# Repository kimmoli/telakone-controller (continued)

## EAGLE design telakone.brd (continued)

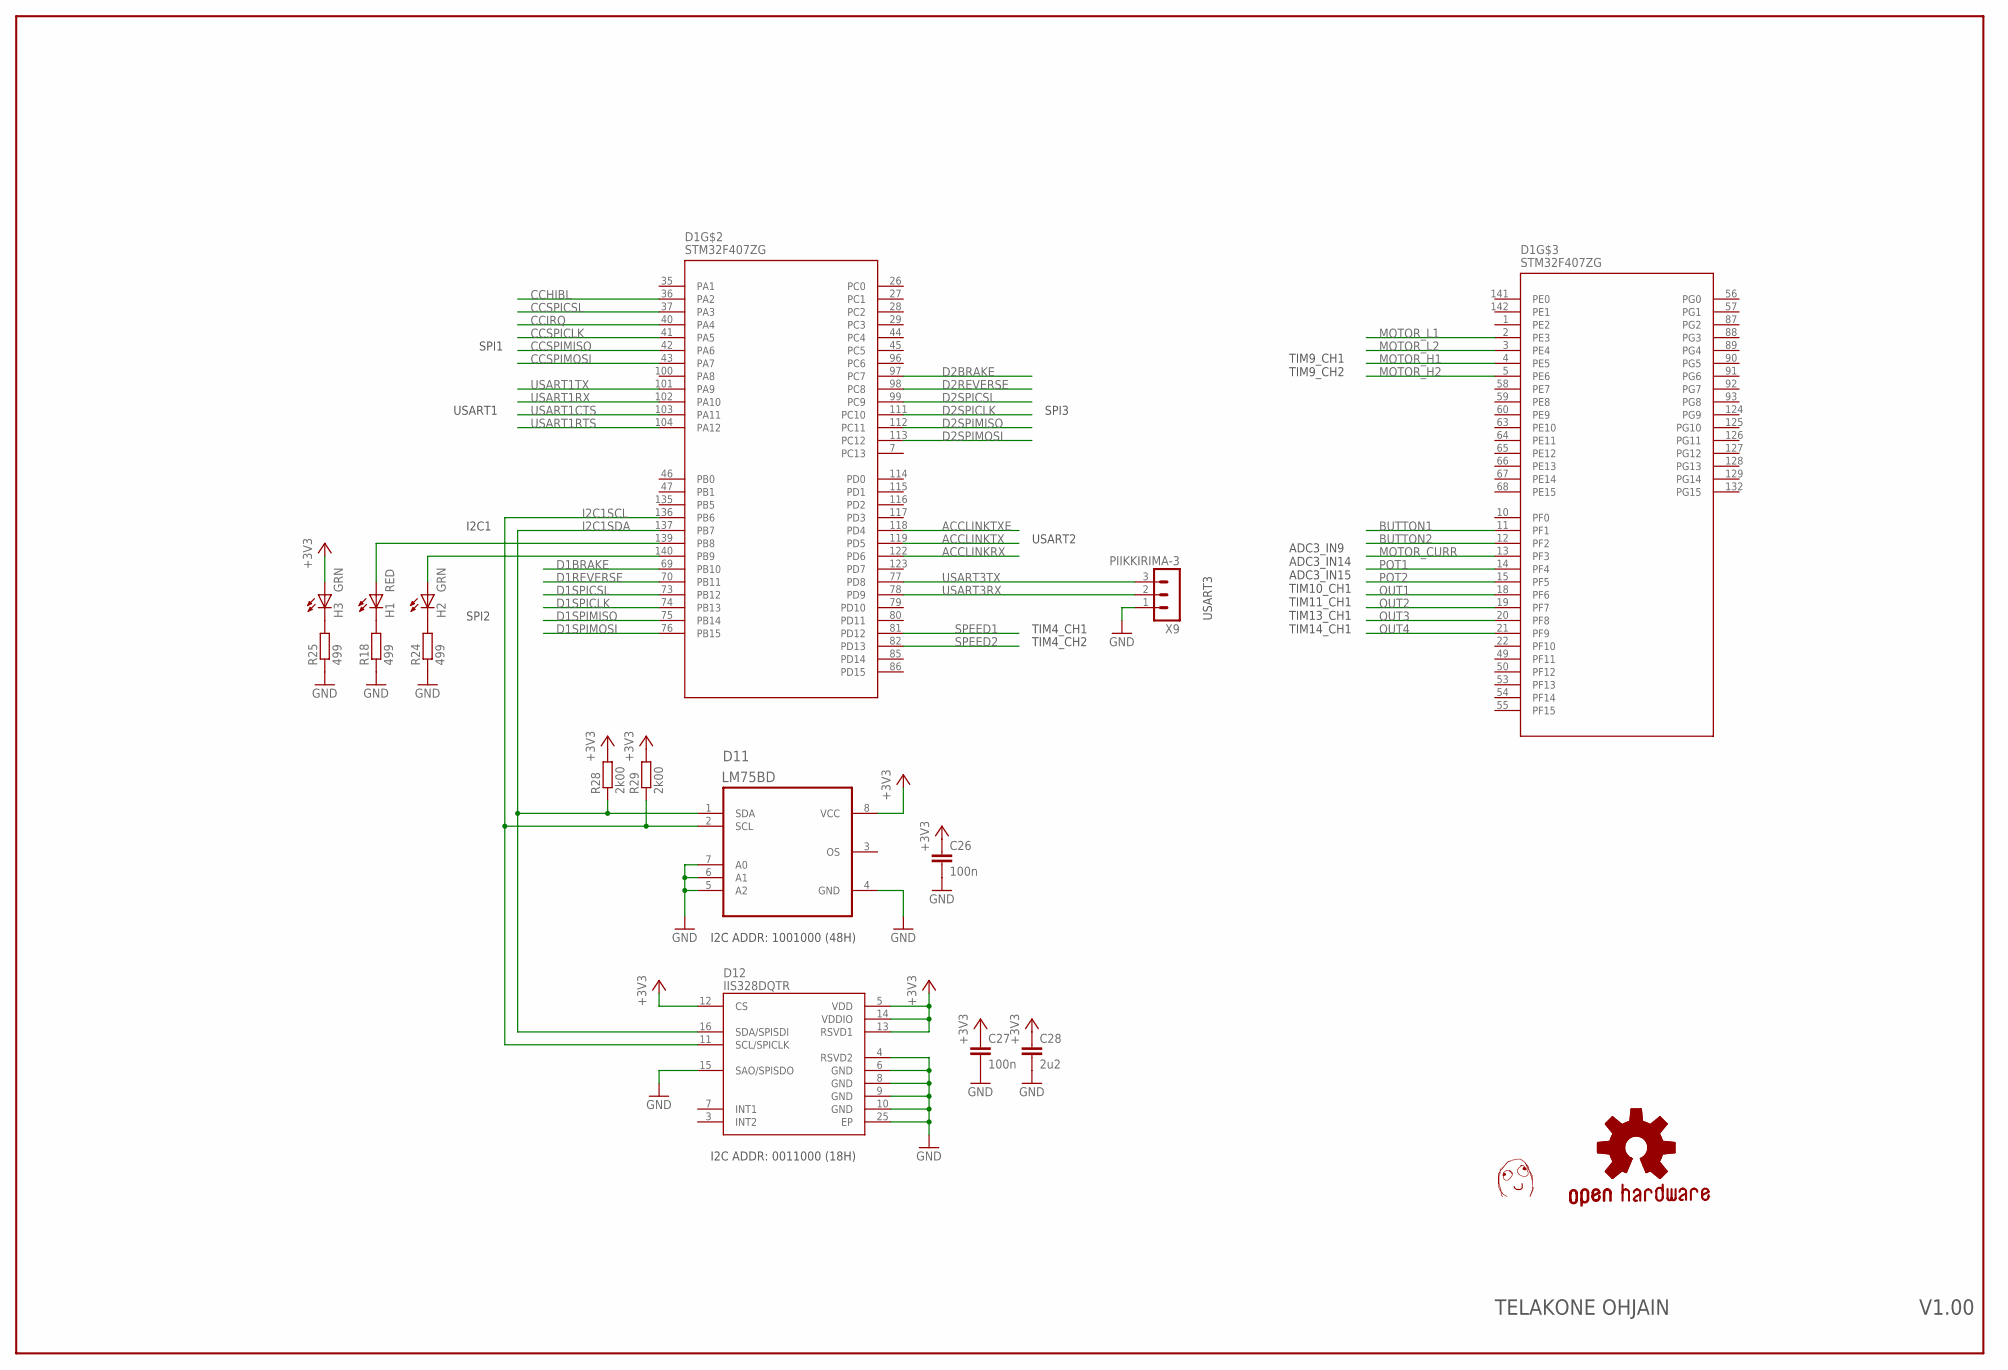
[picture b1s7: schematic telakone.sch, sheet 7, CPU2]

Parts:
C26, C27: 100n; C0603
C28: 2u2; C0603
D1: STM32F407ZG; LQFP-144
D11: LM75BD; SOIC8-N_MC
D12: IIS328DQTR; QFN50P400X400X100-25N
H1: RED; CHIP-LED0603
H2, H3: GRN; CHIP-LED0603
R18, R24, R25: 499; R0603
R28, R29: 2k00; R0603
U$13: DAFUG
X9: PIIKKIRIMA-3

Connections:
+3V3: C26.1, C27.1, C28.1, D11.8 (VCC), D12.5 (VDD), D12.12 (CS), D12.13 (RSVD1), D12.14 (VDDIO), H3.A, R28.2, R29.2; also elsewhere on the board
ACCLINKRX: D1.122 (PD6); also elsewhere on the board
ACCLINKTX: D1.119 (PD5); also elsewhere on the board
ACCLINKTXE: D1.118 (PD4); also elsewhere on the board
BUTTON1: D1.11 (PF1); also elsewhere on the board
BUTTON2: D1.12 (PF2); also elsewhere on the board
CCHIBL: D1.36 (PA2); also elsewhere on the board
CCIRQ: D1.40 (PA4); also elsewhere on the board
CCSPICLK: D1.41 (PA5); also elsewhere on the board
CCSPICSL: D1.37 (PA3); also elsewhere on the board
CCSPIMISO: D1.42 (PA6); also elsewhere on the board
CCSPIMOSI: D1.43 (PA7); also elsewhere on the board
D1BRAKE: D1.69 (PB10); also elsewhere on the board
D1REVERSE: D1.70 (PB11); also elsewhere on the board
D1SPICLK: D1.74 (PB13); also elsewhere on the board
D1SPICSL: D1.73 (PB12); also elsewhere on the board
D1SPIMISO: D1.75 (PB14); also elsewhere on the board
D1SPIMOSI: D1.76 (PB15); also elsewhere on the board
D2BRAKE: D1.97 (PC7); also elsewhere on the board
D2REVERSE: D1.98 (PC8); also elsewhere on the board
D2SPICLK: D1.111 (PC10); also elsewhere on the board
D2SPICSL: D1.99 (PC9); also elsewhere on the board
D2SPIMISO: D1.112 (PC11); also elsewhere on the board
D2SPIMOSI: D1.113 (PC12); also elsewhere on the board
GND: C26.2, C27.2, C28.2, D11.4 (GND), D11.5 (A2), D11.6 (A1), D11.7 (A0), D12.4 (RSVD2), D12.6 (GND), D12.8 (GND), D12.9 (GND), D12.10 (GND), D12.15 (SAO/SPISDO), D12.25 (EP), R18.1, R24.1, R25.1, X9.1; also elsewhere on the board
I2C1SCL: D1.136 (PB6), D11.2 (SCL), D12.11 (SCL/SPICLK), R29.1
I2C1SDA: D1.137 (PB7), D11.1 (SDA), D12.16 (SDA/SPISDI), R28.1
MOTOR_CURR: D1.13 (PF3); also elsewhere on the board
MOTOR_H1: D1.4 (PE5); also elsewhere on the board
MOTOR_H2: D1.5 (PE6); also elsewhere on the board
MOTOR_L1: D1.2 (PE3); also elsewhere on the board
MOTOR_L2: D1.3 (PE4); also elsewhere on the board
unnamed: H2.C, R24.2
unnamed: H1.C, R18.2
unnamed: D1.139 (PB8), H1.A
unnamed: D1.140 (PB9), H2.A
unnamed: H3.C, R25.2
OUT1: D1.18 (PF6); also elsewhere on the board
OUT2: D1.19 (PF7); also elsewhere on the board
OUT3: D1.20 (PF8); also elsewhere on the board
OUT4: D1.21 (PF9); also elsewhere on the board
POT1: D1.14 (PF4); also elsewhere on the board
POT2: D1.15 (PF5); also elsewhere on the board
SPEED1: D1.81 (PD12); also elsewhere on the board
SPEED2: D1.82 (PD13); also elsewhere on the board
USART1CTS: D1.103 (PA11); also elsewhere on the board
USART1RTS: D1.104 (PA12); also elsewhere on the board
USART1RX: D1.102 (PA10); also elsewhere on the board
USART1TX: D1.101 (PA9); also elsewhere on the board
USART3RX: D1.78 (PD9), X9.2
USART3TX: D1.77 (PD8), X9.3

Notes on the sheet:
SPI1
I2C ADDR: 1001000 (48H)
I2C ADDR: 0011000 (18H)
ADC3_IN9 ADC3_IN14 ADC3_IN15 TIM10_CH1 TIM11_CH1 TIM13_CH1 TIM14_CH1
TIM9_CH1 TIM9_CH2
SPI2
SPI3
I2C1
TIM4_CH1
TIM4_CH2
USART2
USART1
USART3
V1.00
TELAKONE OHJAIN

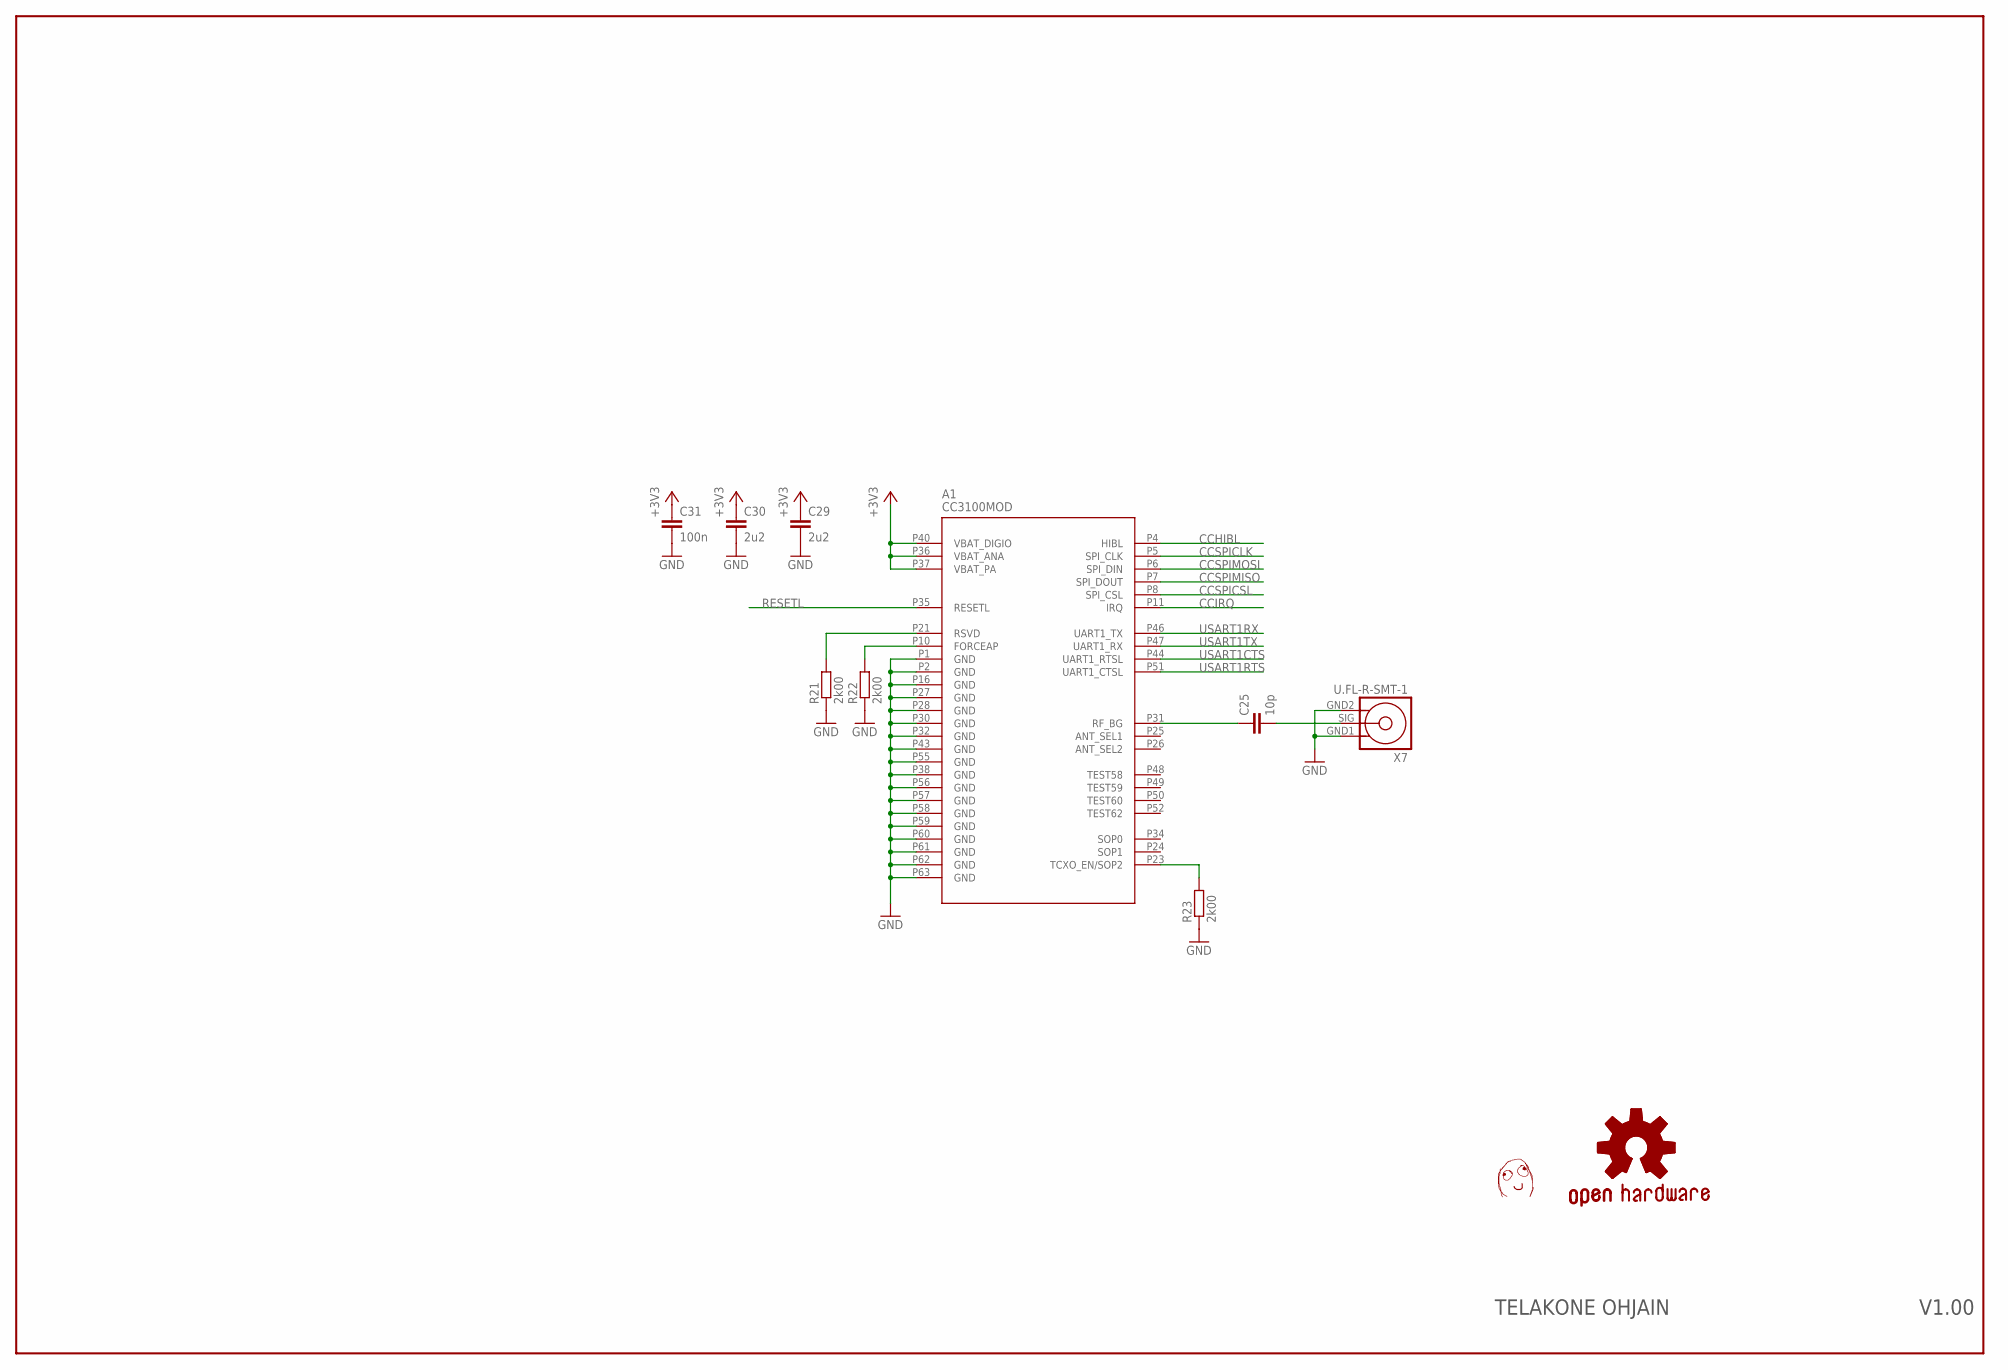
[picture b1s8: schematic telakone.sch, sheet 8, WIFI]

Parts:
A1: CC3100MOD
C25: 10p; C0603
C29, C30: 2u2; C0603
C31: 100n; C0603
R21, R22, R23: 2k00; R0603
U$15: DAFUG
X7: U.FL-R-SMT-1

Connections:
+3V3: A1.P36 (VBAT_ANA), A1.P37 (VBAT_PA), A1.P40 (VBAT_DIGIO), C29.1, C30.1, C31.1; also elsewhere on the board
CCHIBL: A1.P4 (HIBL); also elsewhere on the board
CCIRQ: A1.P11 (IRQ); also elsewhere on the board
CCSPICLK: A1.P5 (SPI_CLK); also elsewhere on the board
CCSPICSL: A1.P8 (SPI_CSL); also elsewhere on the board
CCSPIMISO: A1.P7 (SPI_DOUT); also elsewhere on the board
CCSPIMOSI: A1.P6 (SPI_DIN); also elsewhere on the board
GND: A1.P1 (GND), A1.P2 (GND), A1.P16 (GND), A1.P27 (GND), A1.P28 (GND), A1.P30 (GND), A1.P32 (GND), A1.P38 (GND), A1.P43 (GND), A1.P55 (GND), A1.P56 (GND), A1.P57 (GND), A1.P58 (GND), A1.P59 (GND), A1.P60 (GND), A1.P61 (GND), A1.P62 (GND), A1.P63 (GND), C29.2, C30.2, C31.2, R21.1, R22.1, R23.1, X7.GND1 (1), X7.GND2 (3); also elsewhere on the board
unnamed: A1.P31 (RF_BG), C25.1
unnamed: C25.2, X7.SIG (2)
unnamed: A1.P21 (RSVD), R21.2
unnamed: A1.P10 (FORCEAP), R22.2
unnamed: A1.P23 (TCXO_EN/SOP2), R23.2
RESETL: A1.P35 (RESETL); also elsewhere on the board
USART1CTS: A1.P44 (UART1_RTSL); also elsewhere on the board
USART1RTS: A1.P51 (UART1_CTSL); also elsewhere on the board
USART1RX: A1.P46 (UART1_TX); also elsewhere on the board
USART1TX: A1.P47 (UART1_RX); also elsewhere on the board

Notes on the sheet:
V1.00
TELAKONE OHJAIN

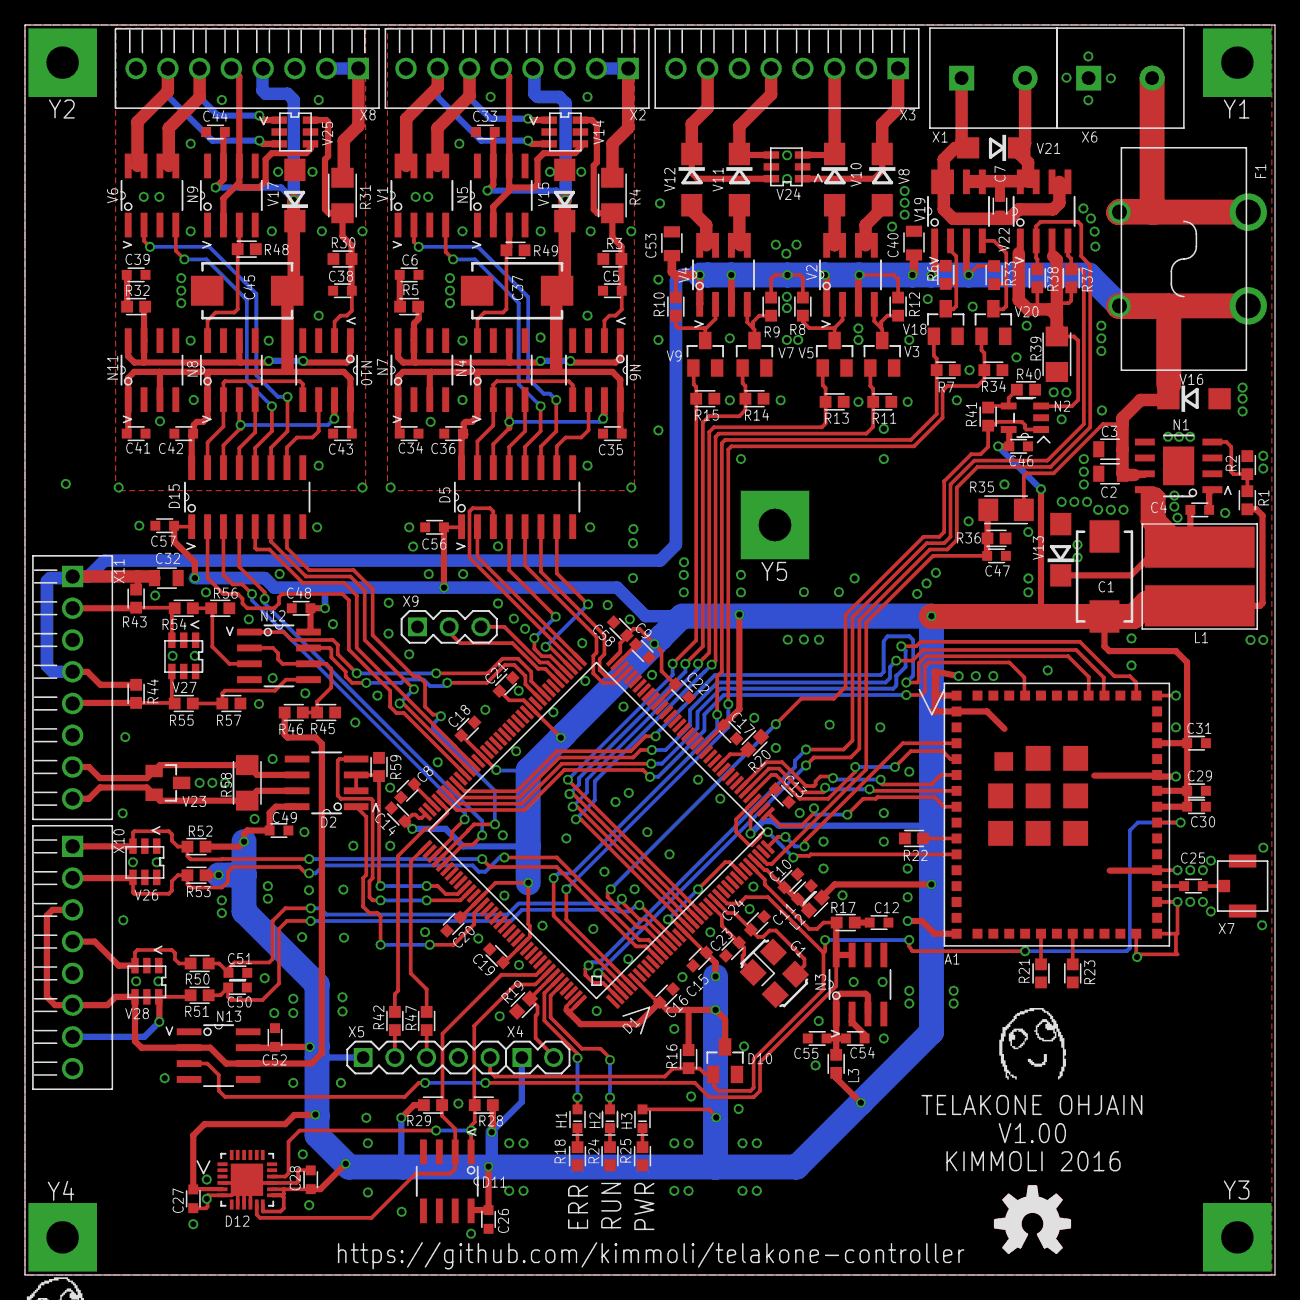
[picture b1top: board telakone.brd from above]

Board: 2 copper layers, 100.0 x 100.0 mm, 196 parts (0 on the bottom side), 137 nets.

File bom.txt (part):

Partlist exported from c:/work/OMAT/telakone/telakone.sch at 3.10.2016 20:16

Qty Value           Device          Package               Parts                                                                                                                                                Description                          
2                   TE_RUUVILIITIN2 TE_RUUVILIITIN2       X1, X6                                                                                                                                                                                    
1   10              RES0603         R0603                 R40                                                                                                                                                                                       
2   100k            RES0603         R0603                 R48, R49                                                                                                                                                                                  
30  100n            CAP0603         C0603                 C10, C13, C14, C15, C16, C17, C18, C19, C20, C21, C22, C26, C27, C31, C33, C34, C35, C36, C41, C42, C43, C44, C46, C48, C49, C52, C55, C56, C57, C58                                      
1   10k0            RES0603         R0603                 R1                                                                                                                                                                                        
7   10n             CAP0603         C0603                 C4, C5, C7, C38, C47, C50, C51                                                                                                                                                            
1   10p             CAP0603         C0603                 C25                                                                                                                                                                                       
1   121 1206        RES1206         R1206                 R58                                                                                                                                                                                       
2   19k1 1206       RES1206         R1206                 R4, R31                                                                                                                                                                                   
5   1k00            RES0603         R0603                 R5, R17, R32, R43, R44                                                                                                                                                                    
3   220u 16V D      CPOL-EUCT7343   CT7343                C1, C37, C45                                                                                                                                         POLARIZED CAPACITOR, European symbol 
2   22p             CAP0603         C0603                 C23, C24                                                                                                                                                                                  
1   25MHz           XTAL_3225_SMD   X_3225                G1                                                                                                                                                   CRYSTAL CLOCK OSCILLATORS            
6   2N7002K         2N7002K         SOT23                 V3, V5, V7, V9, V18, V20                                                                                                                                                                  
26  2k00            RES0603         R0603                 R6, R7, R8, R9, R10, R11, R12, R13, R14, R15, R16, R19, R20, R21, R22, R23, R28, R29, R33, R34, R37, R38, R46, R52, R53, R59                                                              
10  2u2             CAP0603         C0603                 C6, C8, C9, C11, C12, C28, C29, C30, C39, C54                                                                                                                                             
5   2u2 50V 0805    CAP0805         C0805                 C2, C3, C32, C40, C53                                                                                                                                                                     
2   30k1            RES0603         R0603                 R54, R55                                                                                                                                                                                  
9   499             RES0603         R0603                 R18, R24, R25, R41, R42, R45, R47, R50, R51                                                                                                                                               
3   5k90            RES0603         R0603                 R2, R56, R57                                                                                                                                                                              
1   5k90 1206       RES1206         R1206                 R35                                                                                                                                                                                       
3   825             RES0603         R0603                 R3, R30, R36                                                                                                                                                                              
3   AO4803A         AO4803A         SOIC8-N_MC            V2, V4, V19                                                                                                                                                                               
3   AO4886          AO4886          SOIC8-N_MC            V1, V6, V22                                                                                                                                                                               
1   AZV3002S        AZV3002S        SOIC8-N_MC            N12                                                                                                                                                                                       
1   CC3100MOD       CC3100MOD       CC3100MOD             A1                                                                                                                                                                                        
8   DAFUG           DAFUG           DAFUG                 U$1, U$3, U$5, U$7, U$9, U$11, U$13, U$15                                                                                                                                                 
1   ERJ-8BWFR010V   RES1206         R1206                 R39                                                                                                                                                                                       
2   ESDA19SC6       ESDAXXSC6       SOT23-6               V24, V27                                                                                                                                                                                  
2   GRN             LEDCHIP-LED0603 CHIP-LED0603          H2, H3                                                                                                                                               LED                                  
1   IIS328DQTR      IIS328DQTR      QFN50P400X400X100-25N D12                                                                                                                                                                                       
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
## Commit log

2016-09-17 ::beer::
2016-09-17 add placement of isolation group
2016-09-17 move to docs
2016-09-17 initial eagle designs
2016-09-17 p-fet outputs
2016-09-18 placement sketching, temp and acceleration sensors, 2nd drive group
2016-09-18 joystick inputs, change motor driver to plain fets, motor current measurement
2016-09-19 schematic pdf
2016-09-19 add some protection
2016-09-20 Schematics tuning
    Series resistors to SWDIO/SWCLK
    Pulldown to DAC outputs (HighZ after powerup)
    Some missing values added
2016-09-21 speed sensor inputs
2016-09-22 update gitignore
2016-09-22 add accessory link 485 transceiver
2016-09-23 tuning
2016-09-24 placement, all on board
2016-09-24 isolation groups routed
2016-09-25 work commit, routing in progress
2016-09-25 work commit, routing in progress, less than 100 to go :beer:
2016-09-25 less than 100 to go
2016-09-25 fully routed
2016-09-25 Layout finished
2016-09-25 gerbers
2016-09-25 small fixes
2016-09-30 add version label to board
2016-09-30 update documentation
2016-10-03 update component values, add bom
2016-10-07 update schema pdf
2016-10-21 board photo
